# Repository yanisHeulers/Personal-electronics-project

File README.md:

# ±5V Power Supply from 9V Battery

This project implements a compact power supply that generates ±5 V rails from a single 9 V battery.

## Principle

The system works in two stages:

1. A voltage regulator converts the 9 V battery into a stable +5 V supply.
2. A DC-DC converter then generates a −5 V rail from the +5 V supply.

This results in two output voltages:

+5 V  
−5 V

## Tools used
- KiCad (schematic and PCB design)

## Repository structure
Personal-electronics-project
│
├── KiCad-project
│ ├── schematic.kicad_sch
│ ├── pcb.kicad_pcb
│ └── custom_symbols.kicad_sym
│
└── README.md

## Author

Yanis Heulers  
Electrical Engineering Student — Polytechnique Montréal

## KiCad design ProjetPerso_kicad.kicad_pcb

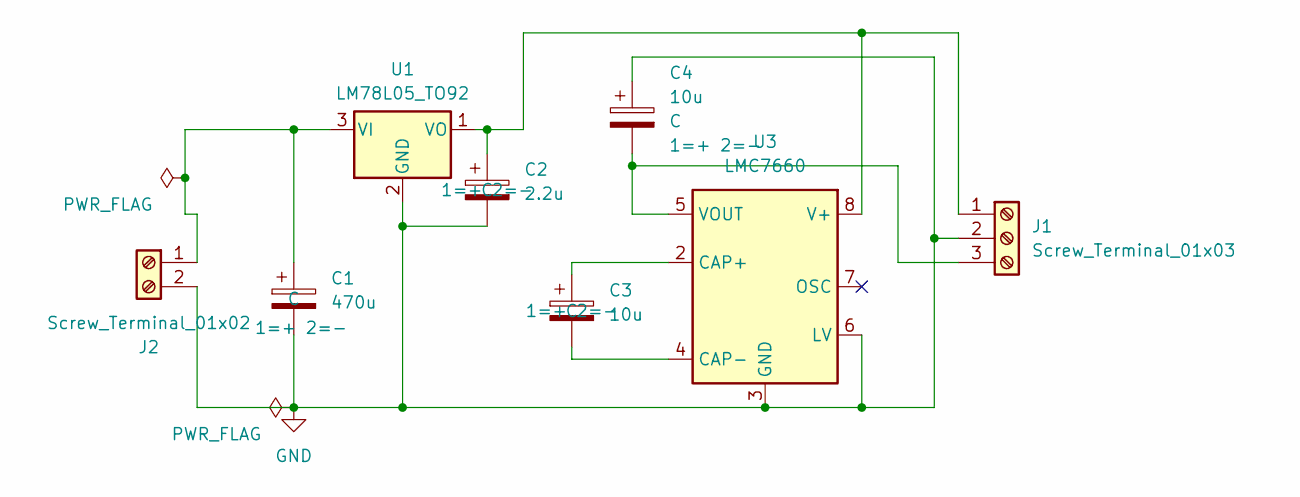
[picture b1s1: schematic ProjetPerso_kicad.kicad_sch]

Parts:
C1: 470u; CP_Radial_D6.3mm_P2.50mm
C2: 2.2u; CP_Radial_D5.0mm_P2.00mm
C3, C4: 10u; CP_Radial_D5.0mm_P2.00mm
J1: Screw_Terminal_01x03; TerminalBlock_Xinya_XY308-2.54-3P_1x03_P2.54mm_Horizontal
J2: Screw_Terminal_01x02; TerminalBlock_bornier-2_P5.08mm
U1: LM78L05_TO92; TO-92_Inline
U3: LMC7660; DIP-8_W7.62mm

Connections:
GND: C1.2, C2.2, C4.1, J1.2, J2.2, U1.2 (GND), U3.3 (GND), U3.6 (LV)
unnamed: C2.1, J1.1, U1.1 (VO), U3.8 (V+)
unnamed: C4.2, J1.3, U3.5 (VOUT)
unnamed: C1.1, J2.1, U1.3 (VI)
unnamed: C3.1, U3.2 (CAP+)
unnamed: C3.2, U3.4 (CAP-)

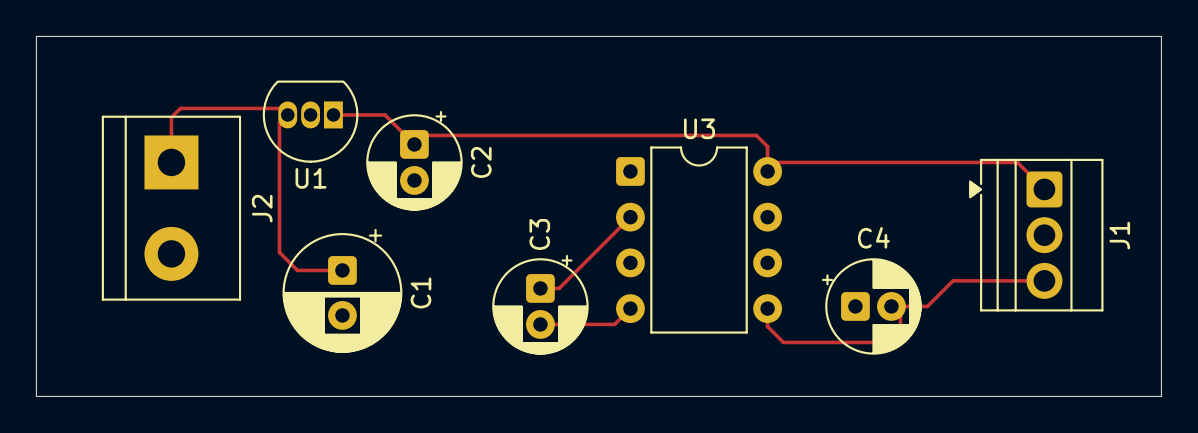
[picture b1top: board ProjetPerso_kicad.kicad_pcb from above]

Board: 2 copper layers, 62.5 x 20.0 mm, 8 parts (0 on the bottom side), 6 nets.

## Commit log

2026-03-11 Create README.md
    Personal electronics projects and simulations (LTspice, MATLAB, KiCad) related to power electronics and control systems.
2026-03-11 Add KiCad project files
